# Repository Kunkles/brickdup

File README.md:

# brickdup

Wireless battery voltage monitor for film/video sets. LoRa sensor nodes tap into camera batteries and broadcast readings to a handheld receiver with an e-ink display.

## Hardware

All boards: **Heltec WiFi LoRa 32 V3** (ESP32-S3 + SX1262, 915 MHz)

Receiver also has: **Waveshare 2.13" e-Paper HAT V4** (250×122, GDEY0213B74)

### Sensor node variants

| Variant | Battery | Connector | Voltage range | Divider |
|---|---|---|---|---|
| Onboard (`OB`) | 4S Li-Ion | D-Tap or AB 4-pin | up to 16.8V | R1=100kΩ, R2=22kΩ |
| Block (`BL`) | 6S Li-Ion | AB 4-pin (inline) | up to 25.2V | R1=180kΩ, R2=27kΩ |

Voltage divider feeds GPIO7. A 100nF ceramic cap between GPIO7 and GND filters ADC noise. Power the MCU through a buck converter (Pololu D24V10F5 — 36V max input, 5V out) tapped off VBAT. **Do not feed VBAT directly to the Heltec USB or VIN pin.**

📐 **Full wiring (both variants, with diagrams): [WIRING.md](WIRING.md)**
📌 **Pin assignments, button controls & screen layouts: [REFERENCE.md](REFERENCE.md)**
📝 **Firmware version history: [CHANGELOG.md](CHANGELOG.md)** — current: **v0.5.9**

### Pin map

```
LoRa SX1262 (HSPI):   CS=8, DIO1=14, RST=12, BUSY=13 | SCK=9, MISO=11, MOSI=10
ADC (sensor nodes):   VBAT_PIN = GPIO7 (ADC1_CH6)
E-ink (receiver):     CS=5, DC=4, RST=3, BUSY=2 | SCK=6, MOSI=1
```

## Sketches

| File | Flash to |
|---|---|
| **`sensor_universal_heltec_v3/`** | **Recommended** node firmware — one board, 4S **or** 6S, type selectable |
| `sensor_onboard_heltec_v3/` | Legacy onboard-only (4S) node |
| `sensor_block_heltec_v3/` | Legacy block-only (6S) node |
| `receiver_wireless_paper_v1_2/` | The handheld receiver (Heltec Wireless Paper) |
| `bench_ping_test/` | Both V3s, to verify the radio link (set `ROLE_PINGER` per board) |

**Universal node** (`sensor_universal_heltec_v3`) replaces the two single-mode
sketches: one universal divider (200k/22k as built — 2×100k + 22k — 6S-safe with headroom) and a runtime **battery
type** (OB 4S / BL 6S) that sets the thresholds + broadcast type. Pick it on the
config page or **long-press PRG** to toggle. Identical firmware on every node —
no per-unit edits. It shows a big 7-segment voltage and the type in the corner.

> **USB test mode:** the node sketches have `USB_TEST_MODE` (default `1`) that
> reads the board's onboard supply (~4V) instead of the divider, so the
> TX → RX → e-ink chain can be validated over USB-C with nothing wired. Set to
> `0` for real monitoring.

## Node identity

Every node has two names:

- **Permanent id** — auto-derived from the chip's unique MAC at boot. Never
  changes, guaranteed unique, and is the WiFi network name + the receiver's
  tracking key. The **universal** sketch uses a type-independent `ND-7F3A` (so
  toggling battery type updates the node in place); the legacy OB/BL sketches
  use `OB-7F3A` / `BL-7F3A`.
- **User name** — the friendly label you assign over WiFi (`Cam A`). Defaults to
  the permanent id until set. Shown on the OLED + handheld and broadcast.

Because the permanent id comes from the silicon, you flash the **same firmware to
every node** — no per-unit edits. With the universal sketch even the battery
type is a runtime setting, so one firmware truly covers every node.

## Packet format

```
T:<type>,I:<permId>,V:<voltage>,S:<status>[,B:<lipo>][,M:<name>]
```

Example: `T:OB,I:OB-7F3A,V:14.73,S:0,B:3.95,M:Cam A`

- `type` — `OB` or `BL`
- `permId` — permanent unique id (chip-derived), receiver's tracking key
- `voltage` — float, 2 decimal places
- `status` — 0=OK, 1=WARN, 2=CRIT, 3=no source (camera battery removed/dead)
- `lipo` — node bridge-LiPo voltage (optional; the node stays alive on it to report S:3)
- `name` — optional friendly name (no commas)

## Naming nodes (WiFi config portal)

Each node hosts a WiFi access point you can join to rename it — no reflashing:

1. Power the node and join WiFi **`Brickdup-OB-7F3A`** (password `brickdup`) —
   the suffix is unique per board, printed on the OLED at boot
2. Open **http://192.168.4.1**
3. Type a **name**, tap Save

The name persists in flash (survives reboot/reflash) and rides along in every
packet, so the handheld shows it automatically.

**Turning WiFi off (saves ~80mA):** no extra hardware needed —

- Tap the node's onboard **PRG button** any time to toggle WiFi on/off, or
- Hit **Turn off WiFi** on the config page when you're done naming.

Press PRG again to bring it back. The on/off choice is **remembered across
reboots** — a node switched off stays off after a power cycle. `WIFI_ON_AT_BOOT`
is only the first-ever-boot default.

## Button controls

| Unit | Single tap | Long press | Triple tap |
|---|---|---|---|
| Node (PRG) | toggle WiFi | — | **power off** |
| Receiver (USER) | page nodes | toggle dashboard | **power off** |

"Power off" is deep sleep (~10–20µA); the screen shows **POWERED DOWN** (white
on black), then **press the button again to wake** (the unit reboots). The
receiver e-ink keeps the POWERED DOWN screen visible while asleep.

Thresholds (defaults, editable per type in the node portal) — Onboard: WARN=13.5V, CRIT=12.8V | Block: WARN=21.0V, CRIT=20.0V

## Radio config

```
Frequency: 915.0 MHz  |  Bandwidth: 125 kHz  |  SF: 9  |  CR: 4/5
Sync word: 0xAB       |  TX power: 17 dBm    |  Preamble: 8
```

All nodes must use identical settings. SF9 gives 50–100m range with obstacles. Up to 12 nodes, 10s interval — no collision concern.

## Build environment

**Arduino IDE 2.x** with the **Heltec ESP32 board package** (Board Manager URL):
```
https://resource.heltec.cn/download/package_heltec_esp32_index.json
```

**Board selection differs per sketch** (the e-ink library requires the exact
board, or it errors with "Wrong build env"):

| Sketch | Tools → Board |
|---|---|
| `receiver_wireless_paper_v1_2` | **Wireless Paper** (search "paper") |
| `sensor_universal_heltec_v3` | Heltec WiFi LoRa 32(V3) |
| `sensor_onboard_heltec_v3` | Heltec WiFi LoRa 32(V3) |
| `sensor_block_heltec_v3` | Heltec WiFi LoRa 32(V3) |

Common settings: USB CDC On Boot → **Enabled** | Upload Speed → 921600

**OTA updates (no USB after the first flash):** every unit's web portal has a
`/update` page. Build a `.bin` via **Sketch → Export Compiled Binary**, join the
unit's WiFi, open its `/update` page (linked from the config page / dashboard),
and upload the matching `.bin` — it flashes the spare partition, verifies, and
reboots. Upload the OB `.bin` to onboard nodes, BL to block nodes, receiver to
the receiver (the page shows which it expects).

> No partition setting needed: the Heltec WiFi LoRa 32 V3 and Wireless Paper
> both default to the `default_8MB` scheme, which already has two ~3.3MB app
> slots (OTA-capable). There's no "Partition Scheme" menu for these boards
> because the partition is fixed — and it's the right one.

### Prebuilt firmware (CI)

GitHub Actions compiles all three sketches on **every push** and on version
tags — no local toolchain needed to get a `.bin`:

- **Every push:** download `brickdup-firmware` from the
  [latest Actions run](../../actions) (artifacts: `brickdup_onboard.bin`,
  `brickdup_block.bin`, `brickdup_receiver.bin`).
- **Tagged releases:** push a `vX.Y.Z` tag → the `.bin`s are attached to a
  [GitHub Release](../../releases).

Grab the matching `.bin` and push it to a unit via its `/update` page. To cut a
release: bump `FW_VERSION` in all three sketches, update `CHANGELOG.md`, commit,
then `git tag v0.5.1 && git push --tags`.

**Libraries (Library Manager):**
- `RadioLib` by Jan Gromeš — all three sketches
- `Heltec ESP32 Dev-Boards` by Heltec — node OLED (`HT_SSD1306Wire.h`)
- `heltec-eink-modules` by todd-herbert — receiver e-ink (pulls in Adafruit GFX)

## BOM

| Part | Source | ~Cost |
|---|---|---|
| Heltec WiFi LoRa 32 V3 (915 MHz) — nodes | Amazon | $22 ea |
| Heltec Wireless Paper (915 MHz) — receiver | Amazon | $22 |
| Pololu D24V10F5 buck converter (per node) | Pololu | — |
| Node LiPo — MakerHawk 1100mAh 1S (JST 1.25) | Amazon `B0F9YSFV4T` | 4-pack |
| Receiver LiPo — MakerFocus 3000mAh 1S (JST 1.25) | Amazon `B08T6GT7DV` | 4-pack |
| D-Tap male connectors | B&H (CT-DTAP-M) | — |
| AB 4-pin connectors | Pinknoise Systems / Trew Audio | — |
| 1% metal film resistors — universal: 200k, 27k (legacy: 100k/22k, 180k/27k) | — | — |
| 100nF ceramic caps (104) | — | — |

## Roadmap

- [x] Bench ping test (verify radio link before analog wiring)
- [x] Receiver paging (USER button cycles pages when >5 nodes)
- [x] Fuel gauge: SoC % + rough time-to-empty per node (voltage-based)
- [x] Calibration (enter true voltage on the web page; gain factor saved to NVS)
- [x] RSSI signal bars per node on the receiver
- [x] Receiver web dashboard (live node table on your phone; long-press USER)
- [x] OTA firmware update via the web portal on all units (/update page)
- [x] Captive portal — config page auto-pops on WiFi connect
- [x] Universal node — one sketch, runtime 4S/6S battery type (web or long-press)
- [x] Prebuilt firmware via CI (GitHub Actions builds .bin on every push)
- [ ] Channel/group selection — separate networks via distinct frequency +
      sync word per channel, set on the node web page and on the receiver,
      NVS-stored. Lets multiple brickdup systems coexist (e.g. 1st/2nd unit)
- [ ] WiFi client (STA) mode — units optionally join a local network (DHCP or
      static IP) instead of hosting their own AP, each reachable at a unique
      mDNS host like `brickdup-7f3a.local` (chip-serial based).
      Credentials set via the AP config page, stored in NVS. Reach/OTA any unit
      from one device on the production WiFi
- [ ] Trusted WiFi networks — a saved list of known SSIDs the unit auto-joins
      (STA) when one is in range and WiFi is on, falling back to its own AP
      otherwise. Set via the config page, stored in NVS
- [ ] BLE / companion phone app — receiver exposes node data over Bluetooth LE
      (GATT, mirroring the `/data` JSON) for a phone app: live view + push
      notifications for CRIT/DEAD batteries (alerts even with the handheld in a
      bag), no WiFi join needed. NimBLE stack; LoRa is a separate radio, BLE
      time-shares 2.4GHz with WiFi
- [ ] iOS app — native companion that keeps a **persistent live readout** of all
      nodes and fires **push/local notifications** on CRIT/DEAD/LOST (even when
      backgrounded or the phone is locked). Connects via BLE (Core Bluetooth
      background mode) to the receiver; the front-end for the BLE item above
- [ ] Bridge LiPo on nodes — small backup cell (buck keeps it charged) so a node
      stays alive to report a **camera battery removed/dead for sure** (vs just
      going silent), survives swaps, and reports its own LiPo level. Replaces the
      receiver's inferred DEAD with an explicit reported one
- [ ] VCLX block-battery mode (NiMH) — the blocks in use are Anton/Bauer
      **VCLX NM2** (600Wh **NiMH**), tapped at a 14.4V 4-pin XLR. Per the
      [manual](https://www.antonbauer.com/wp-content/uploads/2023/07/ab_86750174-4980_0-vclx_nm2-manual_en.pdf)
      spec table, only 28V/48V (+5V USB) are regulated; the 4-pin XLRs are
      **variable 12–17V** (pack-following) — so the node *does* see a real
      discharge curve. But the chemistry breaks the Li-ion fuel gauge: NiMH
      holds a flat ~14.4V (1.2V/cell × 12) for most of the discharge, knees
      at ~13.2V, and the battery hard-cuts its output at **12.0V** (output
      vanishes → bridge LiPo keeps the node alive to report DEAD). Repurpose
      BL mode → NiMH profile: thresholds ≈ WARN 13.2 / CRIT 12.4, and
      suppress SoC%/time-to-empty (or fit a rough NiMH curve) — the Li-ion
      curve reads nonsense on the flat middle. Verify thresholds on a real
      pack: meter the XLR full (~16.8V) vs drained. Heads-up for the divider
      bench test: cap input at ~17V for this mode, not 25.2V
- [ ] CRIT buzzer alert on receiver
- [x] NVS persistence — receiver remembers nodes across reboots (clear on dashboard)
- [ ] Deep sleep on sensor nodes (~10µA between transmissions)
- [ ] PCB design (sensor node, two variants or DNP options)

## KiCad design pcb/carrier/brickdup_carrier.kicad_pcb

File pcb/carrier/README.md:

# brickdup_carrier — v0.2 Heltec V3 carrier board

A carrier/baseboard that **sockets the Heltec WiFi LoRa 32 V3** on 0.1″ female
headers and carries the **unchanged v0.1 buck + divider** power stage
(MP9486A 100 V → 5 V/1 A, 200k/22k sense divider → GPIO7). Replaces the v0.1
wired J2 harness with copper: the only hand-wiring left is the LEMO pigtail
and the optional panel switch/buttons.

**Design lineage:** `pcb/brickdup_psu` (v0.1) — see its README for the full
buck/divider spec, part selection rationale, and layout rules. This README
covers only what v0.2 adds/changes.

---

## 1. What changed vs v0.1

| Area | v0.1 | v0.2 carrier |
|---|---|---|
| Heltec interface | 3-wire JST harness (J2) | **2×18 socket** (HDRA/HDRB), Heltec plugs in |
| 5V / SENSE / GND | wires | copper to socket (5V=HDRB.2, SENSE=HDRA.18/GPIO7) |
| Power switch | none | **SW1** 2-pin JST, in **series** with VBAT (JP1 solder-jumper bypass) |
| Buttons | Heltec onboard only, pressed via lid pistons | **BTN1** (PRG/GPIO0), **BTN2** (RST) 2-pin JSTs → wire to lid/panel buttons anywhere |
| GPIO breakout | none | BRK1 SPI ×8, BRK2 ADC ×8, BRK3 I2C ×4 (unpopulated THT) |
| J1/JST orientation | mouths faced inward (v0.1 bug) | **mouths face off-board** (J1 east, SW1/BTN1/BTN2 south) — asserted in gen_pcb.py |
| D2 clearance | flagged by JLC, de-populated | solver is **courtyard-aware**; D2 placeable |
| Cff | 22 pF DNP | **populated, 470 pF 0603, machine-placed** (bench may still tune the value) |
| Mounting | 2× M2 | 4× M2 (board = enclosure tray) |
| Board | 40×20 mm | **62×44 mm** |

Electronics (values, nets, topology of buck + divider) are **identical** to
v0.1 pending the Cff bench result and any findings from the v0.1 design review.

## 2. Socket pin map (verified vs Heltec HTIT-WB32LA(F)_V3 pin map, 2026-07)

Rows are 18-pin, 2.54 mm pitch. **Pin 1 = GND, at the USB end (board EAST).**
`ROW_SPACING = 22.86 mm` — **✓ VERIFIED 2026-07-02** with calipers on a real
Heltec V3 (measured 22.77–22.93 mm across holes; pitch measured 2.55 mm).

### HDRA — Heltec header J3 (GPIO side, board NORTH row)

| Pin | Heltec | Carrier use |
|---|---|---|
| 1 | GND | GND |
| 2, 3 | 3V3 | 3V3 rail → BRK1/BRK3 |
| 4 | GPIO37 (ADC_Ctrl) | — internal, NC |
| 5, 6 | GPIO46, GPIO45 | — strapping pins, NC |
| 7, 8 | GPIO42, GPIO41 | **I2C → BRK3** (SCL=42, SDA=41) |
| 9, 10 | GPIO40, GPIO39 | — NC (JTAG) |
| 11 | GPIO38 | BRK2.8 |
| 12 | GPIO1 (VBAT_Read) | — internal, NC |
| 13–17 | GPIO2–GPIO6 (ADC1) | **BRK2** generic/ADC |
| 18 | **GPIO7** | **SENSE** (divider midpoint — same firmware pin as v0.1/wired) |

### HDRB — Heltec header J2 (power side, board SOUTH row)

| Pin | Heltec | Carrier use |
|---|---|---|
| 1 | GND | GND |
| 2 | **5V** | **+5V from buck** (powers Heltec + charges its LiPo) |
| 3, 4 | Ve | — NC |
| 5, 6 | GPIO44 RX, GPIO43 TX | — NC (USB serial) |
| 7 | **RST** | **BTN2** JST |
| 8 | **GPIO0** (PRG/USER_SW) | **BTN1** JST |
| 9 | GPIO36 (Vext ctrl) | — internal, NC |
| 10–12 | GPIO35, 34, 33 | **BRK1** (SPI cluster) |
| 13, 14 | GPIO47, GPIO48 | **BRK1** |
| 15 | GPIO26 | BRK1.8 |
| 16 | GPIO21 (OLED_RST) | — internal, NC |
| 17, 18 | GPIO20, GPIO19 | — NC (ADC2/USB) |

## 3. Switch, buttons, breakouts

- **SW1 (power switch, series):** J1 VBAT → `VBATIN` → SW1 → `VBAT` → buck.
  Wire a panel toggle/slide switch to the SW1 JST. **No switch? Bridge JP1**
  (solder jumper next to J1) and leave SW1 empty. Switch must be rated ≥30 V DC
  at ~1 A (it carries raw battery, max 25.2 V).
- **BTN1 = PRG (GPIO0→GND), BTN2 = RST (RST→GND):** momentary N.O. buttons,
  wired anywhere (lid flexures, panel). Parallel with the Heltec's onboard
  buttons — both keep working. All firmware gestures (tap/long/triple on
  GPIO0) work unchanged.
- **Breakouts (unpopulated 2.54 mm THT, DNP in BOM):**
  - **BRK1 "SPI"** (south): 3V3, GND, IO33, IO34, IO35, IO47, IO48, IO26 —
    six GPIOs + power = future W5500/SPI module lands here.
  - **BRK2 "ADC"** (north): 5V, GND, IO2–IO6 (ADC1/touch), IO38.
  - **BRK3 "I2C"** (north): 3V3, GND, IO41 (SDA), IO42 (SCL).

## 4. Floorplan

```
        N (ADC + I2C breakouts, north strip)
  ┌────────────────────────────────────────────┐
  │ O   [BRK2 ADC........]   [BRK3 I2C..]   O  │   O = M2 holes ×4
  │ ══HDRA════════════════════════════pin1══   │   Heltec rows: pin1 EAST
  │  ANT│ divider  │  buck island   │        │ │   (USB end → east wall)
  │     │ R1 R2 C1 │ Cout L1 D1 U1 Cin D2│ [J1]│ ← VBAT in, mouth EAST
  │ ══HDRB════════════════════════════pin1══   │   JP1 bypass near J1
  │ O  [SW1] [BTN1] [BTN2]  [BRK1 SPI.....] O  │
  └────────────────────────────────────────────┘
        S (switch + buttons, mouths off south edge)
```

- Buck island sits **between the socket rows under the Heltec** — the socket
  gives ~8.5 mm clearance, enough for L1 (~5 mm). It's biased **east (USB
  end)**, keeping the switch node away from the SX1262/antenna end (west).
- Sense divider isolated **west**, far from the SW node, short run to HDRA.18.
- The Heltec module outline (50.2×25.5) is drawn on silk with USB/ANT marks.

## 5. Assembly notes

- Socket rows = THT **female pin sockets** (2×18-pin 1×18 strips, **8.5 mm
  standard height — not low-profile**, that height is what clears L1 under the
  module). Order with **JLC's THT/hand-solder assembly** so the board arrives
  fully built — the design goal is zero soldering for us (no SMD by hand).
  Heltec ships with matching male pins.
- **No-switch option without soldering:** instead of bridging the JP1 solder
  jumper, crimp a wire loop into a 2-pin JST-PH plug and park it in SW1.
- BRK1–3 are **DNP** — solder headers only when a project needs them.
- JSTs (J1, SW1, BTN1, BTN2) are the same S2B-PH-SM4-TB as v0.1 (LCSC C295747).
- Cff ships **JLC-populated at 470 pF** (no hand-soldering). If the v0.1 bench test
  lands on a different value, update the BOM line before ordering.

## 5a. Known issues (v0.2 bench, 2026-07-23)

- **USB power while socketed doesn't boot the Heltec (backfeed).** The
  module's 5V pin is hard-wired to the buck output, so USB-powering a
  socketed module with the carrier unpowered backfeeds the +5V net: current
  flows backward through L1 and U1's high-side body diode into the input
  caps and VBAT net. U1 then sees ~4.3 V VIN (5 V minus a diode drop) —
  bottom edge of the MP9486A's operating range — and can chatter against
  the rail that's feeding it; with the USB port's current limit on top, the
  module gets a sagging/dirty 5 V and won't boot (symptom: dead OLED, only
  the no-battery charge LED blinking; module boots fine on USB out of the
  socket).
  - **Workaround:** whenever USB is plugged with the module socketed
    (flashing, config portal at the bench), power the carrier too — 15 V on
    J1, SW1 closed — so the buck owns the rail and nothing backfeeds.
  - **v0.3 candidate fix:** diode (Schottky, or ideal-diode e.g. LM66100)
    between buck output and the socket 5V pin; if Schottky, trim the FB
    divider so the post-diode rail lands at ~5.0 V.

## 6. Reproducible pipeline

Same toolchain as v0.1 (see `pcb/HANDOFF.md` §7). From `pcb/carrier/`:

```
python3 gen_kicad.py                  # schematic (ERC: 0 violations)
python3 gen_pcb.py                    # outline+socket+solver placement (courtyard-aware)
python3 ../export_dsn.py brickdup_carrier.kicad_pcb /tmp/carrier.dsn
java -jar /tmp/freerouting224.jar -de /tmp/carrier.dsn -do /tmp/carrier.ses -mp 12
python3 apply_route.py                # import + vias + solid GND on connectors + fill
kicad-cli pcb drc brickdup_carrier.kicad_pcb -o /tmp/drc.json --format json --severity-error
python3 fix_thermals.py brickdup_carrier.kicad_pcb /tmp/drc.json   # heal starved thermals
kicad-cli pcb drc brickdup_carrier.kicad_pcb   # -> 0 violations, 0 unconnected
```

**freerouting gotcha:** if it routes but never writes the SES, set
`"gui": {"enabled": false}` in its `freerouting.json` (under
`$TMPDIR/freerouting/`) — with `gui.enabled=true` the headless run finishes
routing and then hangs waiting on a GUI handoff instead of saving.

## 7. Open items before ordering

1. ~~ROW_SPACING~~ **✓ verified 22.86 mm** (calipers, 2026-07-02). Still worth
   eyeballing **pin-1/GND at the USB end** when the sockets arrive (test-fit the
   Heltec on loose sockets before soldering them).
2. Cff is populated at **470 pF** — if the v0.1 bench test says otherwise, change the BOM value before ordering.
3. Fold in any v0.1 **design-review findings** (EN threshold, EP thermal vias).
4. **Enclosure v2** dry-fit plan — see `enclosure/CARRIER_ENCLOSURE.md`.
5. LCSC codes for: pin sockets 1×18 (e.g. C2337recheck), pin headers (DNP —
   no code needed), plus carry-over v0.1 BOM codes.

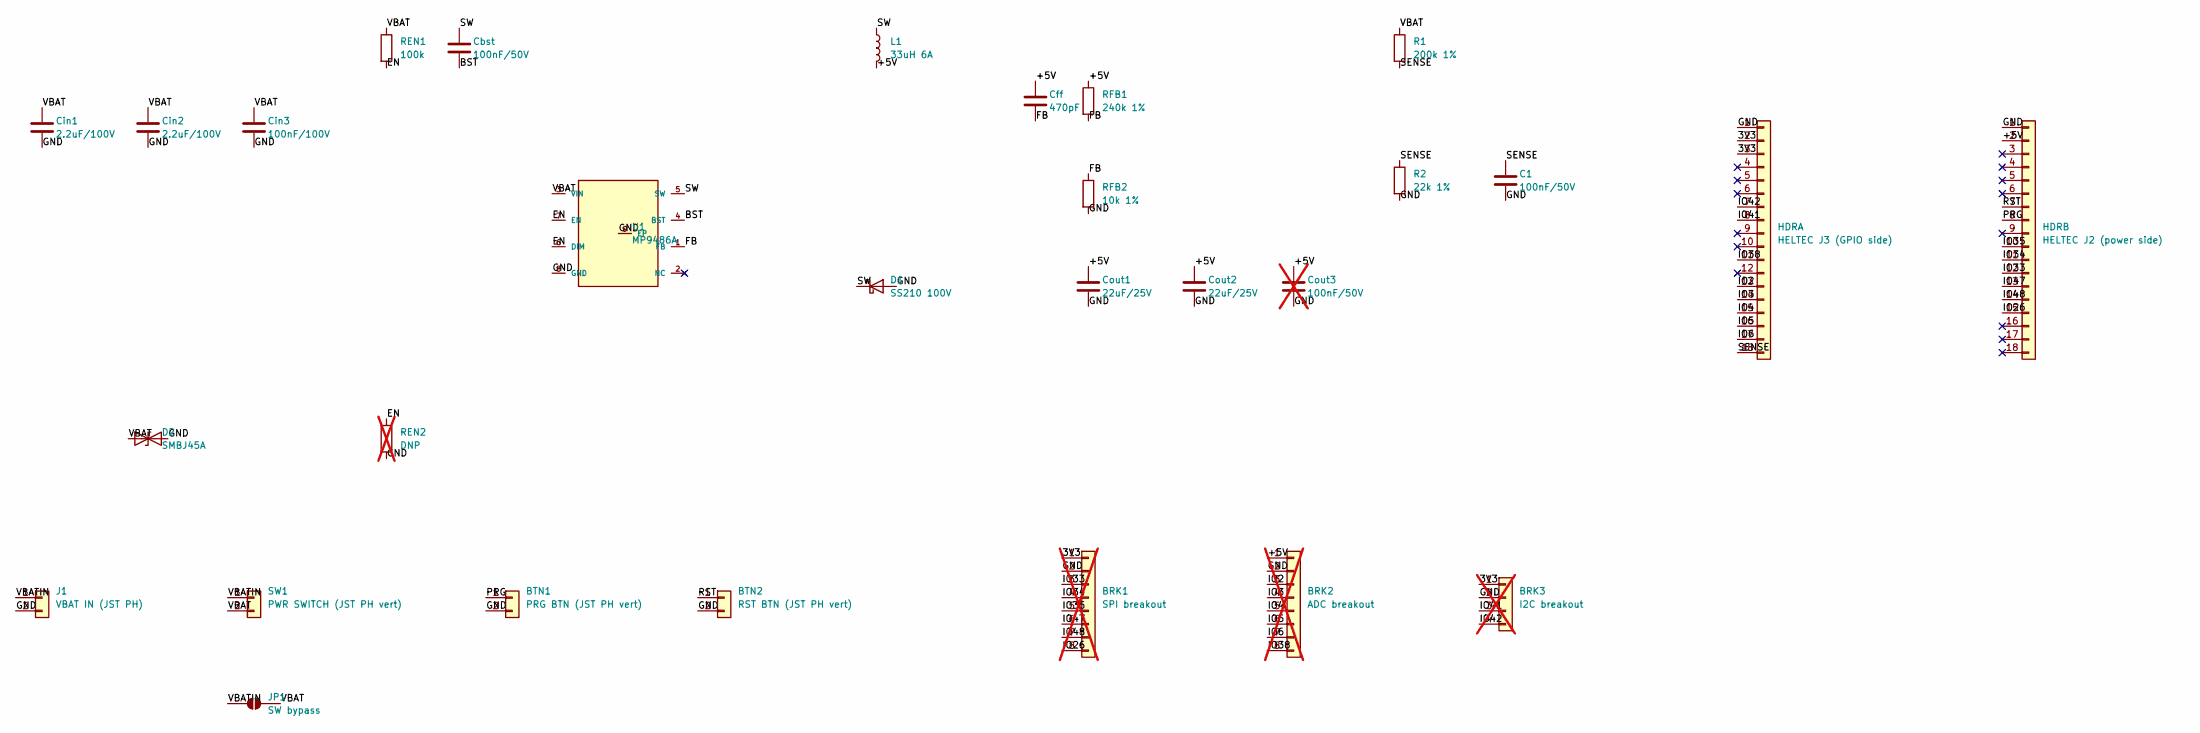
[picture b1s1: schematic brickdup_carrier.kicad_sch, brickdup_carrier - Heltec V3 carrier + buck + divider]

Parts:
BRK1: SPI breakout; PinHeader_1x08_P2.54mm_Vertical; not fitted
BRK2: ADC breakout; PinHeader_1x08_P2.54mm_Vertical; not fitted
BRK3: I2C breakout; PinHeader_1x04_P2.54mm_Vertical; not fitted
BTN1: PRG BTN (JST PH vert); JST_PH_B2B-PH-K_1x02_P2.00mm_Vertical
BTN2: RST BTN (JST PH vert); JST_PH_B2B-PH-K_1x02_P2.00mm_Vertical
C1: 100nF/50V; C_0603_1608Metric
Cbst: 100nF/50V; C_0402_1005Metric
Cff: 470pF; C_0603_1608Metric
Cin1, Cin2: 2.2uF/100V; C_1210_3225Metric
Cin3: 100nF/100V; C_0603_1608Metric
Cout1, Cout2: 22uF/25V; C_1206_3216Metric
Cout3: 100nF/50V; C_0402_1005Metric; not fitted
D1: SS210 100V; D_SMA
D2: SMBJ45A; D_SMB
HDRA: HELTEC J3 (GPIO side); PinSocket_1x18_P2.54mm_Vertical
HDRB: HELTEC J2 (power side); PinSocket_1x18_P2.54mm_Vertical
J1: VBAT IN (JST PH); JST_PH_S2B-PH-SM4-TB_1x02-1MP_P2.00mm_Horizontal
JP1: SW bypass; SolderJumper-2_P1.3mm_Open_TrianglePad1.0x1.5mm
L1: 33uH 6A; L_CYA0850
R1: 200k 1%; R_0805_2012Metric
R2: 22k 1%; R_0805_2012Metric
REN1: 100k; R_0402_1005Metric
REN2: DNP; R_0402_1005Metric; not fitted
RFB1: 240k 1%; R_0402_1005Metric
RFB2: 10k 1%; R_0402_1005Metric
SW1: PWR SWITCH (JST PH vert); JST_PH_B2B-PH-K_1x02_P2.00mm_Vertical
U1: MP9486A; SOIC-8-1EP_3.9x4.9mm_P1.27mm_EP2.41x3.3mm

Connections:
3V3: BRK1.1, BRK3.1, HDRA.2, HDRA.3
+5V: BRK2.1, Cff.1, Cout1.1, Cout2.1, Cout3.1, HDRB.2, L1.2, RFB1.1
BST: Cbst.2, U1.4 (BST)
EN: REN1.2, REN2.1, U1.6 (DIM), U1.7 (EN)
FB: Cff.2, RFB1.2, RFB2.1, U1.1 (FB)
GND: BRK1.2, BRK2.2, BRK3.2, BTN1.2, BTN2.2, C1.2, Cin1.2, Cin2.2, Cin3.2, Cout1.2, Cout2.2, Cout3.2, D1.2 (A), D2.2 (A2), HDRA.1, HDRB.1, J1.2, R2.2, REN2.2, RFB2.2, U1.8 (GND), U1.9 (EP)
IO2: BRK2.3, HDRA.13
IO3: BRK2.4, HDRA.14
IO4: BRK2.5, HDRA.15
IO5: BRK2.6, HDRA.16
IO6: BRK2.7, HDRA.17
IO26: BRK1.8, HDRB.15
IO33: BRK1.3, HDRB.12
IO34: BRK1.4, HDRB.11
IO35: BRK1.5, HDRB.10
IO38: BRK2.8, HDRA.11
IO41: BRK3.3, HDRA.8
IO42: BRK3.4, HDRA.7
IO47: BRK1.6, HDRB.13
IO48: BRK1.7, HDRB.14
PRG: BTN1.1, HDRB.8
RST: BTN2.1, HDRB.7
SENSE: C1.1, HDRA.18, R1.2, R2.1
SW: Cbst.1, D1.1 (K), L1.1, U1.5 (SW)
VBAT: Cin1.1, Cin2.1, Cin3.1, D2.1 (A1), JP1.2 (B), R1.1, REN1.1, SW1.2, U1.3 (VIN)
VBATIN: J1.1, JP1.1 (A), SW1.1

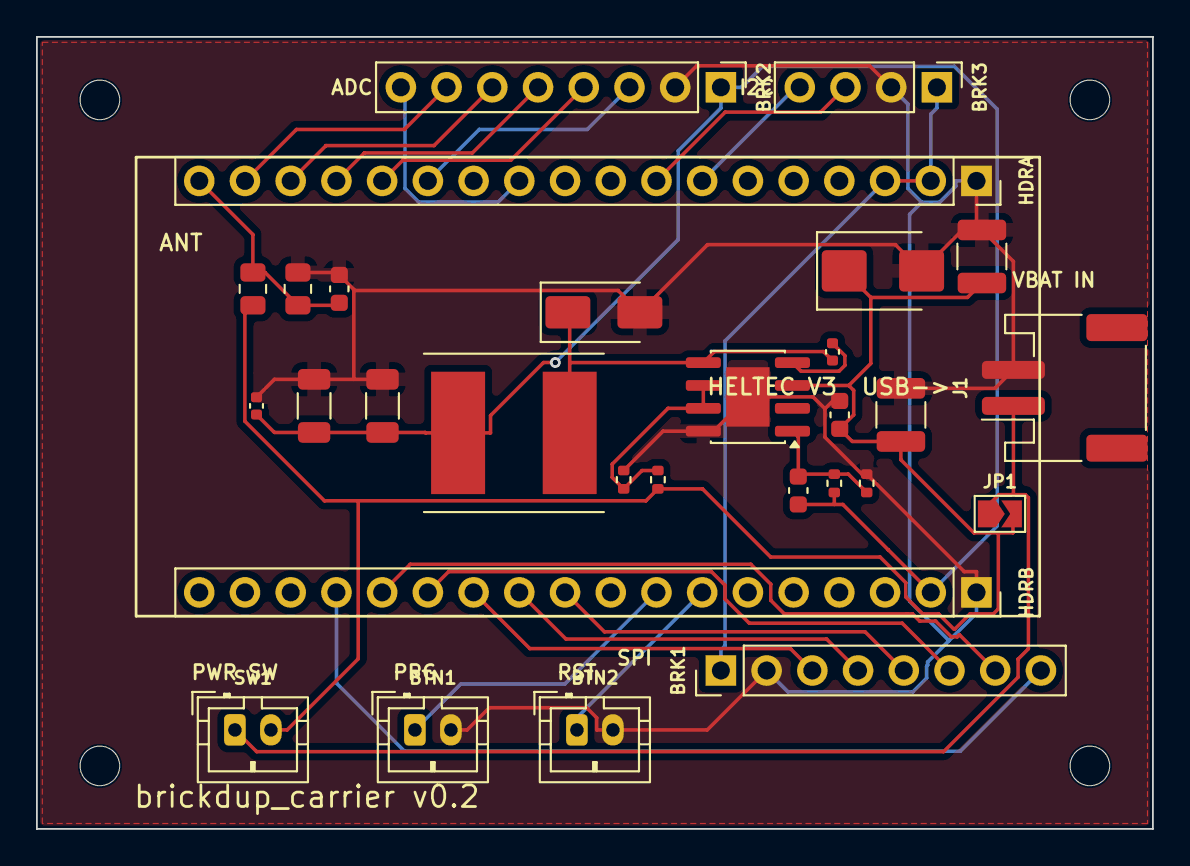
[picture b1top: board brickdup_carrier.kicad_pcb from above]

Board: 2 copper layers, 62.0 x 44.0 mm, 33 parts (0 on the bottom side), 26 nets.

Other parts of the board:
H1, H2, H3, H4: MountingHole_2.2mm_M2

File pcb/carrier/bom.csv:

Comment,Designator,Footprint,LCSC Part #
MP9486AGN-Z 100V buck,U1,SOIC-8-EP,C404013
33uH 6A inductor CYA0850,L1,brickdup:L_CYA0850,C19268648
Schottky 100V 2A SS210,D1,SMA (DO-214AC),C14996
TVS SMBJ45A,D2,SMB (DO-214AA),C42371744
2.2uF 100V X7R,Cin1,C_1210,C55151
2.2uF 100V X7R,Cin2,C_1210,C55151
100nF 50V X7R,Cin3,C_0603,C14663
100nF 16V X7R,Cbst,C_0402,C1525
22uF 25V X5R,Cout1,C_1206,C12891
22uF 25V X5R,Cout2,C_1206,C12891
470pF 50V X7R (ripple injection),Cff,C_0603,C22396
240k 1% 0402,RFB1,R_0402,C64043
10k 1% 0402,RFB2,R_0402,C25744
100k 1% 0402,REN1,R_0402,C25741
200k 1% 0805,R1,R_0805,C17539
22k 1% 0805,R2,R_0805,C17560
100nF 50V X7R,C1,C_0603,C14663
JST PH 2-pin SMD side (VBAT in),J1,JST_PH_S2B-PH-SM4-TB,C295747
JST PH 2-pin THT vertical (power switch),SW1,JST_PH_B2B-PH-K_Vertical,C131337
JST PH 2-pin THT vertical (PRG button),BTN1,JST_PH_B2B-PH-K_Vertical,C131337
JST PH 2-pin THT vertical (RST button),BTN2,JST_PH_B2B-PH-K_Vertical,C131337
"Female header 1x18 2.54mm THT, 8.5mm height (NOT low-profile) - PICK IN JLC BOM MATCHER",HDRA,PinSocket_1x18_P2.54mm_Vertical,
"Female header 1x18 2.54mm THT, 8.5mm height (NOT low-profile) - PICK IN JLC BOM MATCHER",HDRB,PinSocket_1x18_P2.54mm_Vertical,
DNP - solder jumper (bare copper),JP1,SolderJumper-2_P1.3mm_Open,
DNP - 100nF output HF,Cout3,C_0402,
DNP - EN divider bottom,REN2,R_0402,
DNP - SPI breakout header,BRK1,PinHeader_1x08,
DNP - ADC breakout header,BRK2,PinHeader_1x08,
DNP - I2C breakout header,BRK3,PinHeader_1x04,
